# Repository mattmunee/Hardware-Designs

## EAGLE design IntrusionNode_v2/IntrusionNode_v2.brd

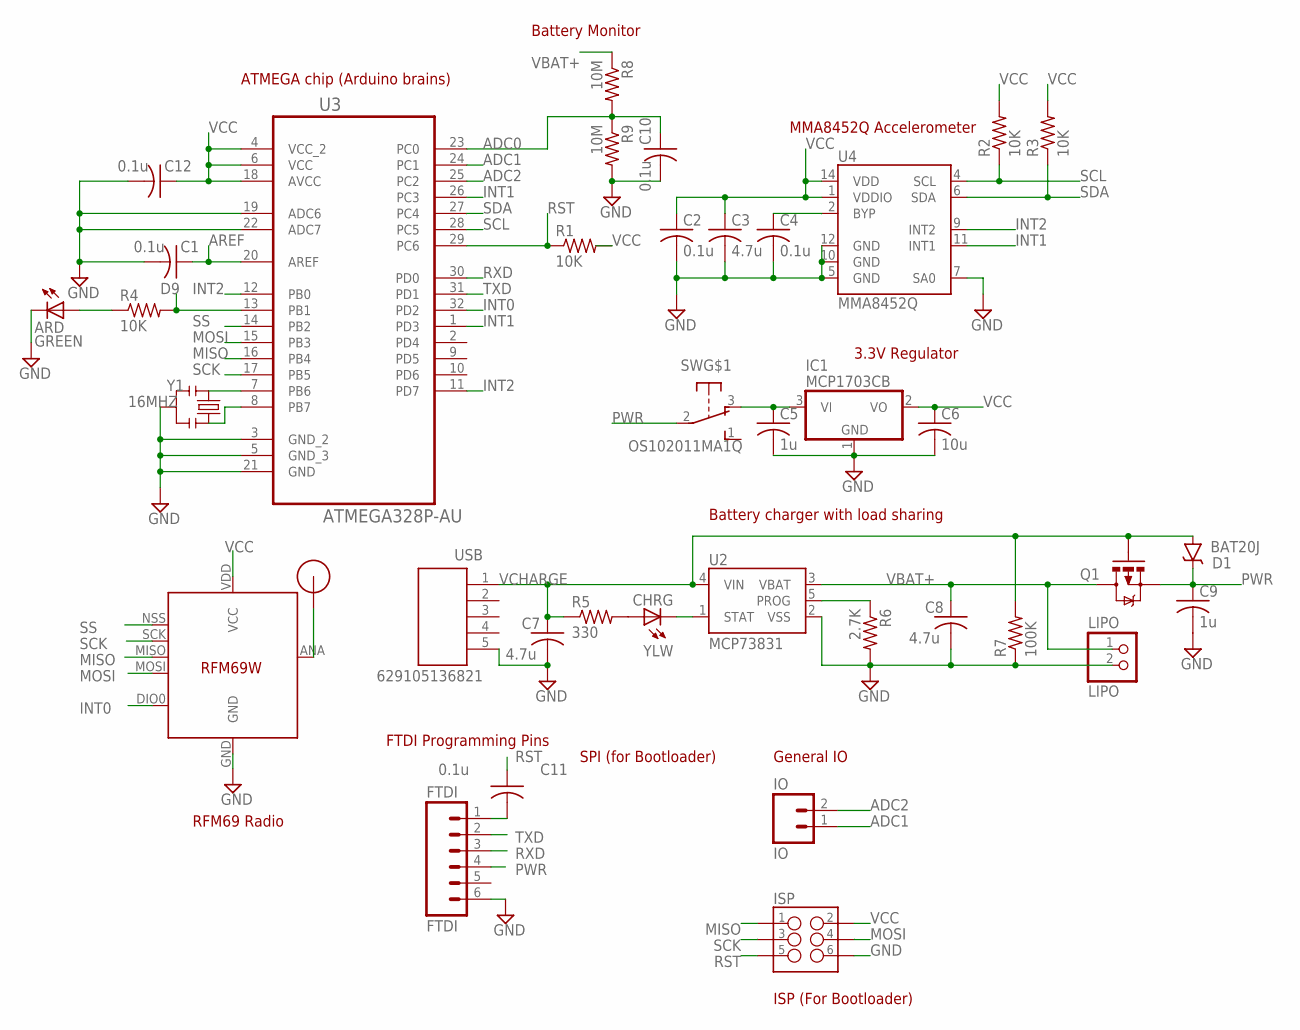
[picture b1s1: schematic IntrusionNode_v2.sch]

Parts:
ANT: RFM12B_ANTENNA; RFM12B-ANTENNA; PARTNO *
ARD: GREEN; CHIPLED_0805; PARTNO LG R971-KN-1
C1, C2, C4, C10, C11, C12: 0.1u; C0805; PARTNO CL21B104KBCNNNC
C3, C7, C8: 4.7u; C0805; PARTNO CL21A475KPFNNNE
C5, C9: 1u; C0805; PARTNO CL21B105KPFNNNE
C6: 10u; C0805; PARTNO CL21B106KPQNNNE
CHRG: YLW; CHIPLED_0805; PARTNO LY R976-PS-36
D1: BAT20J; SOD-323; PARTNO BAT20JFILM
FTDI: FTDI; 1X06_LOCK_LONGPADS; PARTNO 0022284363
IC1: MCP1703CB; SOT23; PARTNO MCP1703T-3302E/CB
IO: IO; 1X02_LOCK_LONGPADS; PARTNO 0022284363
ISP: M03X2NO_SILK; 2X3-NS; PARTNO 0010897060
LIPO: LIPO; JST-PH-2-SMT-RA; PARTNO S2B-PH-SM4-TB(LF)(SN)
Q1: MOSFET-PCHANNELSMD; SOT23-3; PARTNO PMV48XP,215
R1, R2, R3, R4: 10K; R0805; PARTNO RC2012J103CS
R5: 330; R0805; PARTNO RC2012J331CS
R6: 2.7K; R0805; PARTNO RC2012J272CS
R7: 100K; R0805; PARTNO RC2012J104CS
R8, R9: 10M; R0805; PARTNO RC2012F106CS
SW: OS102011MA1Q; PARTNO OS102011MA1QN1
U1: RFM69; RFM69W-MINPADS; PARTNO RFM69W
U2: MCP73831; SOT23-5; PARTNO MCP73831T-2ATI/OT
U3: ATMEGA328P-AU; QFP80P900X900X120-32N; PARTNO ATMEGA328P-AUR
U4: MMA8452Q; QFN-16_0.5MM; PARTNO MMA8452QT
USB: 629105136821; PARTNO 629105136821
Y1: 16MHZ; X3-SMD-3.6X1.3X0.8MM; PARTNO CSTCE16M0V53-R0

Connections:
ADC0: C10.1, R8.2, R9.1, U3.23 (PC0)
ADC1: IO.1, U3.24 (PC1)
ADC2: IO.2, U3.25 (PC2)
AREF: C1.1, U3.20 (AREF)
D9: R4.2, U3.13 (PB1)
GND: ARD.C, C1.2, C2.2, C3.2, C4.2, C5.2, C6.2, C7.2, C8.2, C9.2, C10.2, C12.2, FTDI.6, IC1.1 (GND), ISP.6, LIPO.2 (1), R6.2, R7.1, R9.2, U1.GND, U2.2 (VSS), U3.3 (GND_2), U3.5 (GND_3), U3.19 (ADC6), U3.21 (GND), U3.22 (ADC7), U4.5 (GND), U4.7 (SA0), U4.10 (GND), U4.12 (GND), USB.5, Y1.2
INT0: U1.DIO0, U3.32 (PD2)
INT1: U3.1 (PD3), U3.26 (PC3), U4.11 (INT1)
INT2: U3.11 (PD7), U3.12 (PB0), U4.9 (INT2)
MISO: ISP.1, U1.MISO, U3.16 (PB4)
MOSI: ISP.4, U1.MOSI, U3.15 (PB3)
unnamed: U3.7 (PB6), Y1.1
unnamed: U3.8 (PB7), Y1.3
unnamed: C4.1, U4.2 (BYP)
unnamed: ANT.P$1, U1.ANA (ANT)
unnamed: ARD.A, R4.1
unnamed: R6.1, U2.5 (PROG)
unnamed: CHRG.C, U2.1 (STAT)
unnamed: CHRG.A, R5.2
unnamed: C11.2, FTDI.1
unnamed: C5.1, IC1.3 (VI), SW.3 (O)
PWR: C9.1, D1.C, FTDI.4, Q1.2 (S), SW.2
RST: C11.1, ISP.5, R1.1, U3.29 (PC6)
RXD: FTDI.3, U3.30 (PD0)
SCK: ISP.3, U1.SCK, U3.17 (PB5)
SCL: R2.1, U3.28 (PC5), U4.4 (SCL)
SDA: R3.1, U3.27 (PC4), U4.6 (SDA)
SS: U1.NSS (SEL), U3.14 (PB2)
TXD: FTDI.2, U3.31 (PD1)
VBAT+: C8.1, LIPO.1 (2), Q1.3 (D), R8.1, U2.3 (VBAT)
VCC: C2.1, C3.1, C6.1, C12.1, IC1.2 (VO), ISP.2, R1.2, R2.2, R3.2, U1.VDD (VCC), U3.4 (VCC_2), U3.6 (VCC), U3.18 (AVCC), U4.1 (VDDIO), U4.14 (VDD)
VCHARGE: C7.1, D1.A, Q1.1 (G), R5.1, R7.2, U2.4 (VIN), USB.1

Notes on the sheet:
Battery Monitor
ATMEGA chip (Arduino brains)
RFM69 Radio
Battery charger with load sharing
FTDI Programming Pins
SPI (for Bootloader)
General IO
3.3V Regulator
MMA8452Q Accelerometer
ISP (For Bootloader)

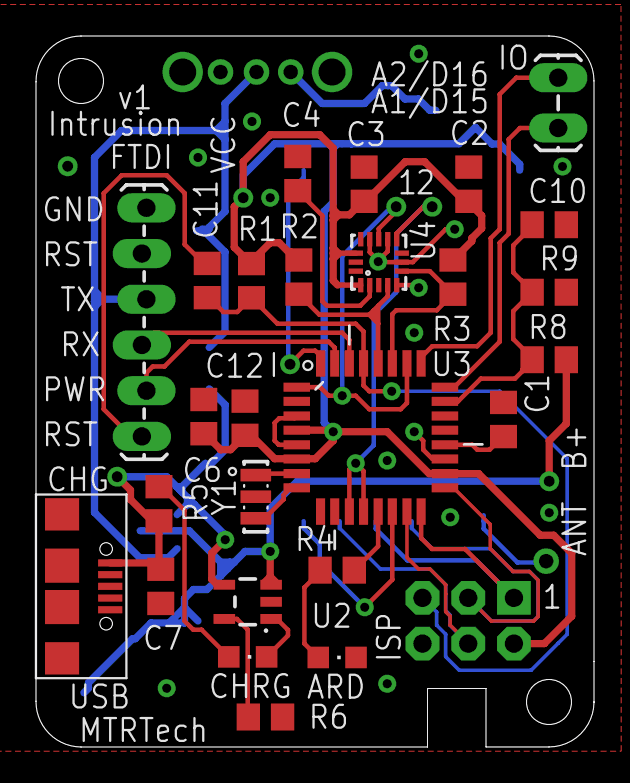
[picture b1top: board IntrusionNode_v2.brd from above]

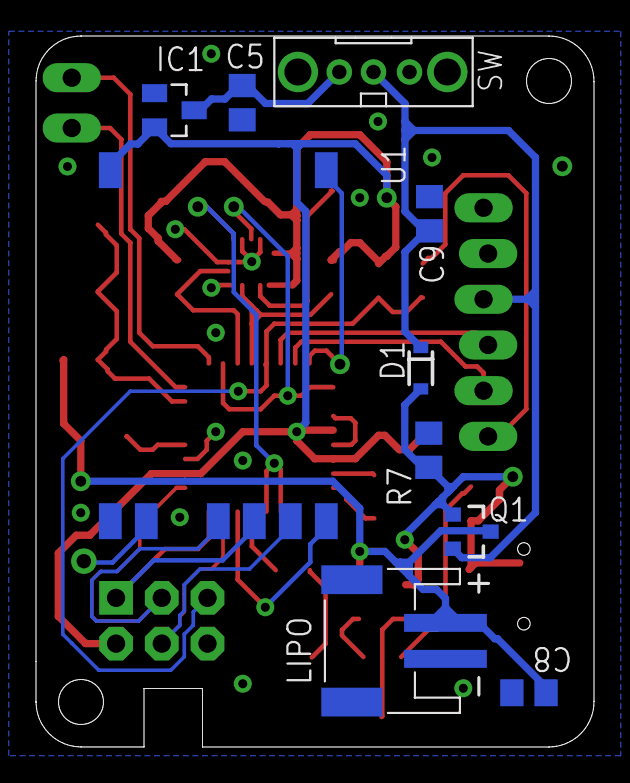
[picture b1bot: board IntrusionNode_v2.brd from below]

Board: 2 copper layers, 31.0 x 39.5 mm, 38 parts (10 on the bottom side), 32 nets.

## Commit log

2015-08-18 Commit current IntrusionNode design
2015-08-24 First commit of intrusion node
2015-08-25 *** Parts order place on Digikey
    Web ID 149351856 Access ID 51215 Salesorder Number 43979223 Submitted 8/25/2015 4:06:46 PM
    Modified board, adding notch, also changed part numbers for diode
    and MOSFET to reduce current.
2015-08-28 ** Place OSH Park Order Number Er6KsneG, project name IntrusionNode_v2_150827

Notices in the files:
parts and their libraries:
SparkFun-PowerIC: Licensing: Creative Commons ShareAlike 4.0 International - https://creativecommons.org/licenses/by-sa/4.0
SparkFun-Connectors: Licensing: CC v3.0 Share-Alike You are welcome to use this library for commercial purposes.
